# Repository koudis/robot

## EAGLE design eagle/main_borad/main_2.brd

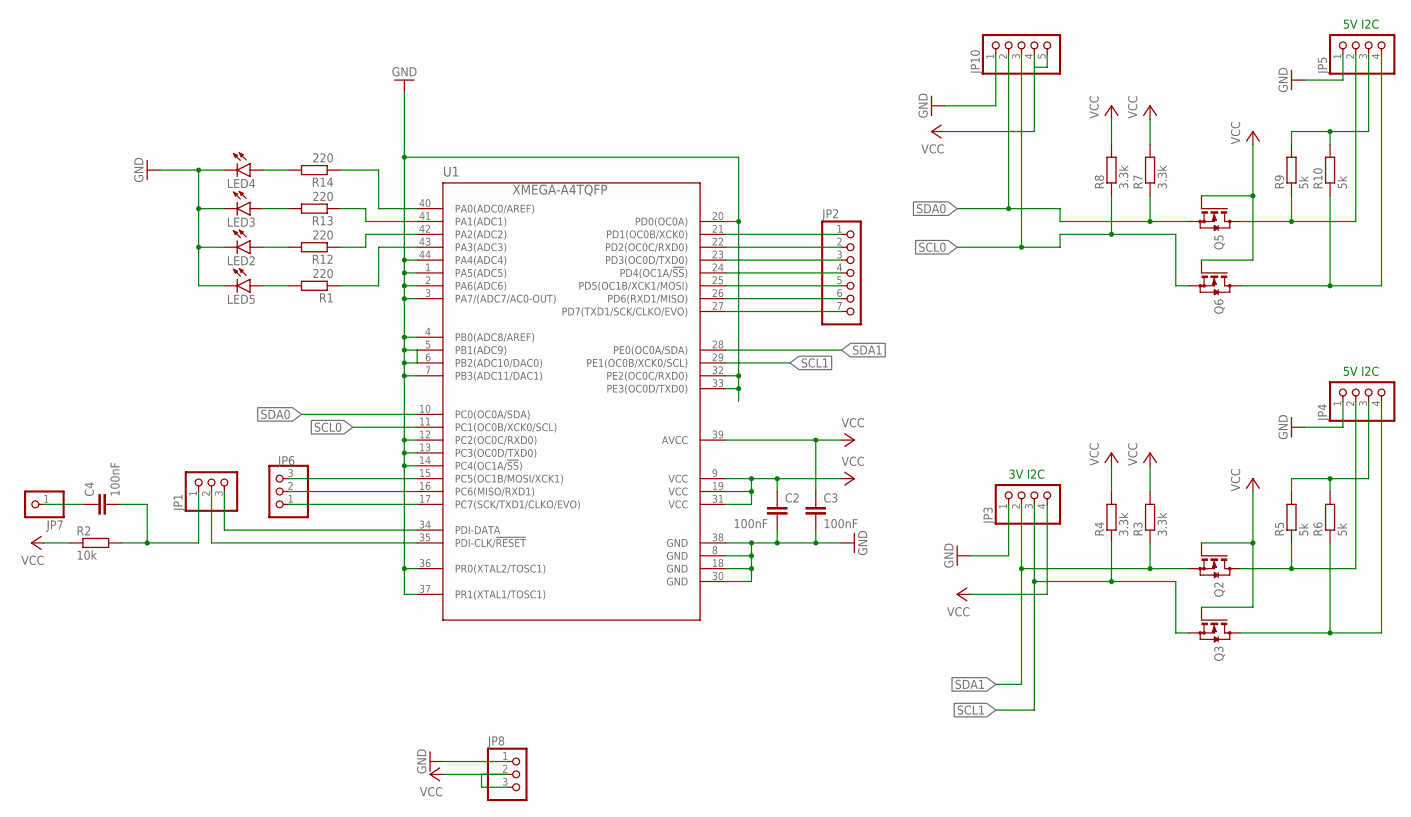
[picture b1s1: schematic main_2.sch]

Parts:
C2, C3, C4: 100nF; C0805
JP1, JP6, JP8: PINHD-1X3; 1X03
JP2: PINHD-1X7; 1X07
JP3, JP4, JP5: PINHD-1X4; 1X04
JP7: PINHD-1X1; 1X01
JP10: PINHD-1X5; 1X05
LED2, LED3, LED4, LED5: LED1206; LED-1206
Q2, Q3, Q5, Q6: BSS123; SOT23
R1, R12, R13, R14: 220; R0805
R2: 10k; R0805
R3, R4, R7, R8: 3.3k; R0805
R5, R6, R9, R10: 5k; R0805
U1: XMEGA-A4TQFP; TQFP44

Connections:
GND: C2.2, C3.2, JP3.1, JP4.1, JP5.1, JP8.1, JP10.1, LED2.C, LED3.C, LED4.C, LED5.C, U1.1 (PA5(ADC5)), U1.2 (PA6(ADC6)), U1.3 (PA7/(ADC7/AC0-OUT)), U1.4 (PB0(ADC8/AREF)), U1.5 (PB1(ADC9)), U1.6 (PB2(ADC10/DAC0)), U1.7 (PB3(ADC11/DAC1)), U1.8 (GND), U1.12 (PC2(OC0C/RXD0)), U1.13 (PC3(OC0D/TXD0)), U1.14 (PC4(OC1A/!SS!)), U1.18 (GND), U1.20 (PD0(OC0A)), U1.30 (GND), U1.32 (PE2(OC0C/RXD0)), U1.33 (PE3(OC0D/TXD0)), U1.36 (PR0(XTAL2/TOSC1)), U1.37 (PR1(XTAL1/TOSC1)), U1.38 (GND), U1.44 (PA4(ADC4))
unnamed: C4.2, JP1.1, R2.2
unnamed: JP1.2, U1.35 (PDI-CLK/!RESET)
unnamed: JP6.1, U1.17 (PC7(SCK/TXD1/CLKO/EVO))
unnamed: JP2.5, U1.25 (PD5(OC1B/XCK1/MOSI))
unnamed: JP2.6, U1.26 (PD6(RXD1/MISO))
unnamed: JP2.3, U1.23 (PD3(OC0D/TXD0))
unnamed: JP2.2, U1.22 (PD2(OC0C/RXD0))
unnamed: JP4.2, Q2.3 (D), R5.1
unnamed: JP4.4, Q3.3 (D), R6.1
unnamed: JP1.3, U1.34 (PDI-DATA)
unnamed: JP2.1, U1.21 (PD1(OC0B/XCK0))
unnamed: JP2.4, U1.24 (PD4(OC1A/!SS!))
unnamed: JP2.7, U1.27 (PD7(TXD1/SCK/CLKO/EVO))
unnamed: JP4.3, R5.2, R6.2
unnamed: JP6.2, U1.16 (PC6(MISO/RXD1))
unnamed: JP6.3, U1.15 (PC5(OC1B/MOSI/XCK1))
unnamed: JP5.2, Q5.3 (D), R9.1
unnamed: JP5.4, Q6.3 (D), R10.1
unnamed: JP5.3, R9.2, R10.2
unnamed: R1.1, U1.43 (PA3(ADC3))
unnamed: R12.1, U1.42 (PA2(ADC2))
unnamed: R13.1, U1.41 (PA1(ADC1))
unnamed: R14.1, U1.40 (PA0(ADC0/AREF))
unnamed: LED5.A, R1.2
unnamed: LED2.A, R12.2
unnamed: LED3.A, R13.2
unnamed: LED4.A, R14.2
RESET: C4.1, JP7.1
SCL0: JP10.3, Q6.2 (S), R8.1, U1.11 (PC1(OC0B/XCK0/SCL))
SCL1: JP3.3, Q3.2 (S), R4.1, U1.29 (PE1(OC0B/XCK0/SCL))
SDA0: JP10.2, Q5.2 (S), R7.1, U1.10 (PC0(OC0A/SDA))
SDA1: JP3.2, Q2.2 (S), R3.1, U1.28 (PE0(OC0A/SDA))
VCC: C2.1, C3.1, JP3.4, JP8.2, JP8.3, JP10.4, JP10.5, Q2.1 (G), Q3.1 (G), Q5.1 (G), Q6.1 (G), R2.1, R3.2, R4.2, R7.2, R8.2, U1.9 (VCC), U1.19 (VCC), U1.31 (VCC), U1.39 (AVCC)

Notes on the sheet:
5V I2C
3V I2C

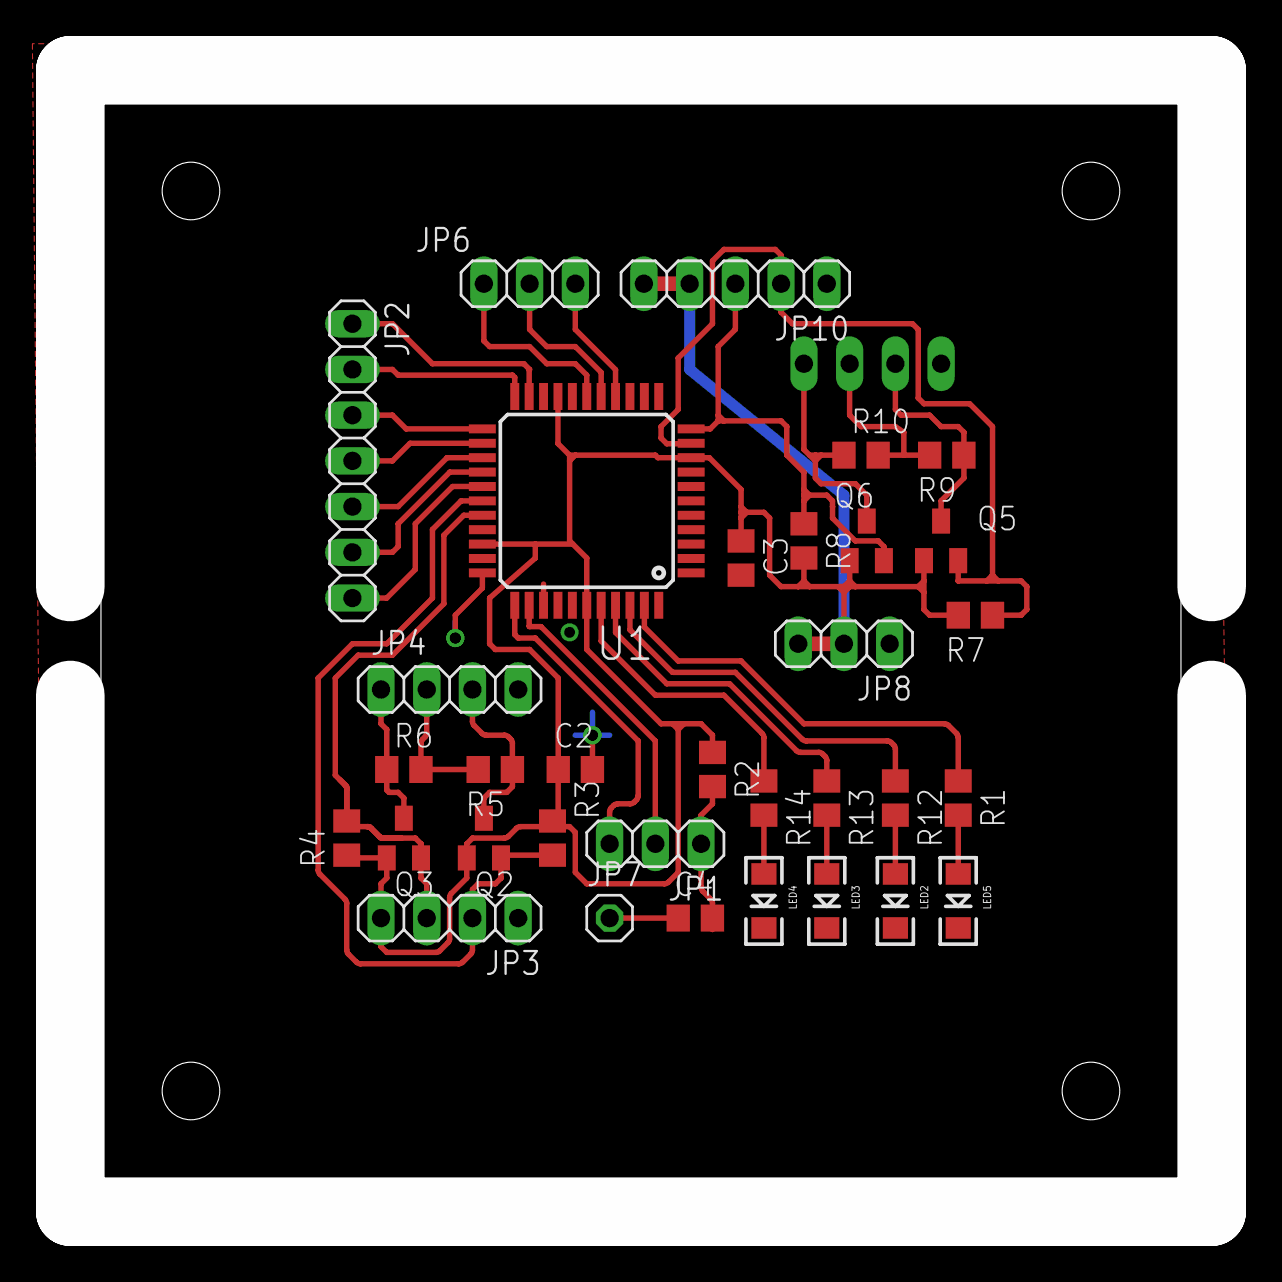
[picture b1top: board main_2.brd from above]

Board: 2 copper layers, 63.4 x 63.4 mm, 34 parts (1 on the bottom side), 34 nets.

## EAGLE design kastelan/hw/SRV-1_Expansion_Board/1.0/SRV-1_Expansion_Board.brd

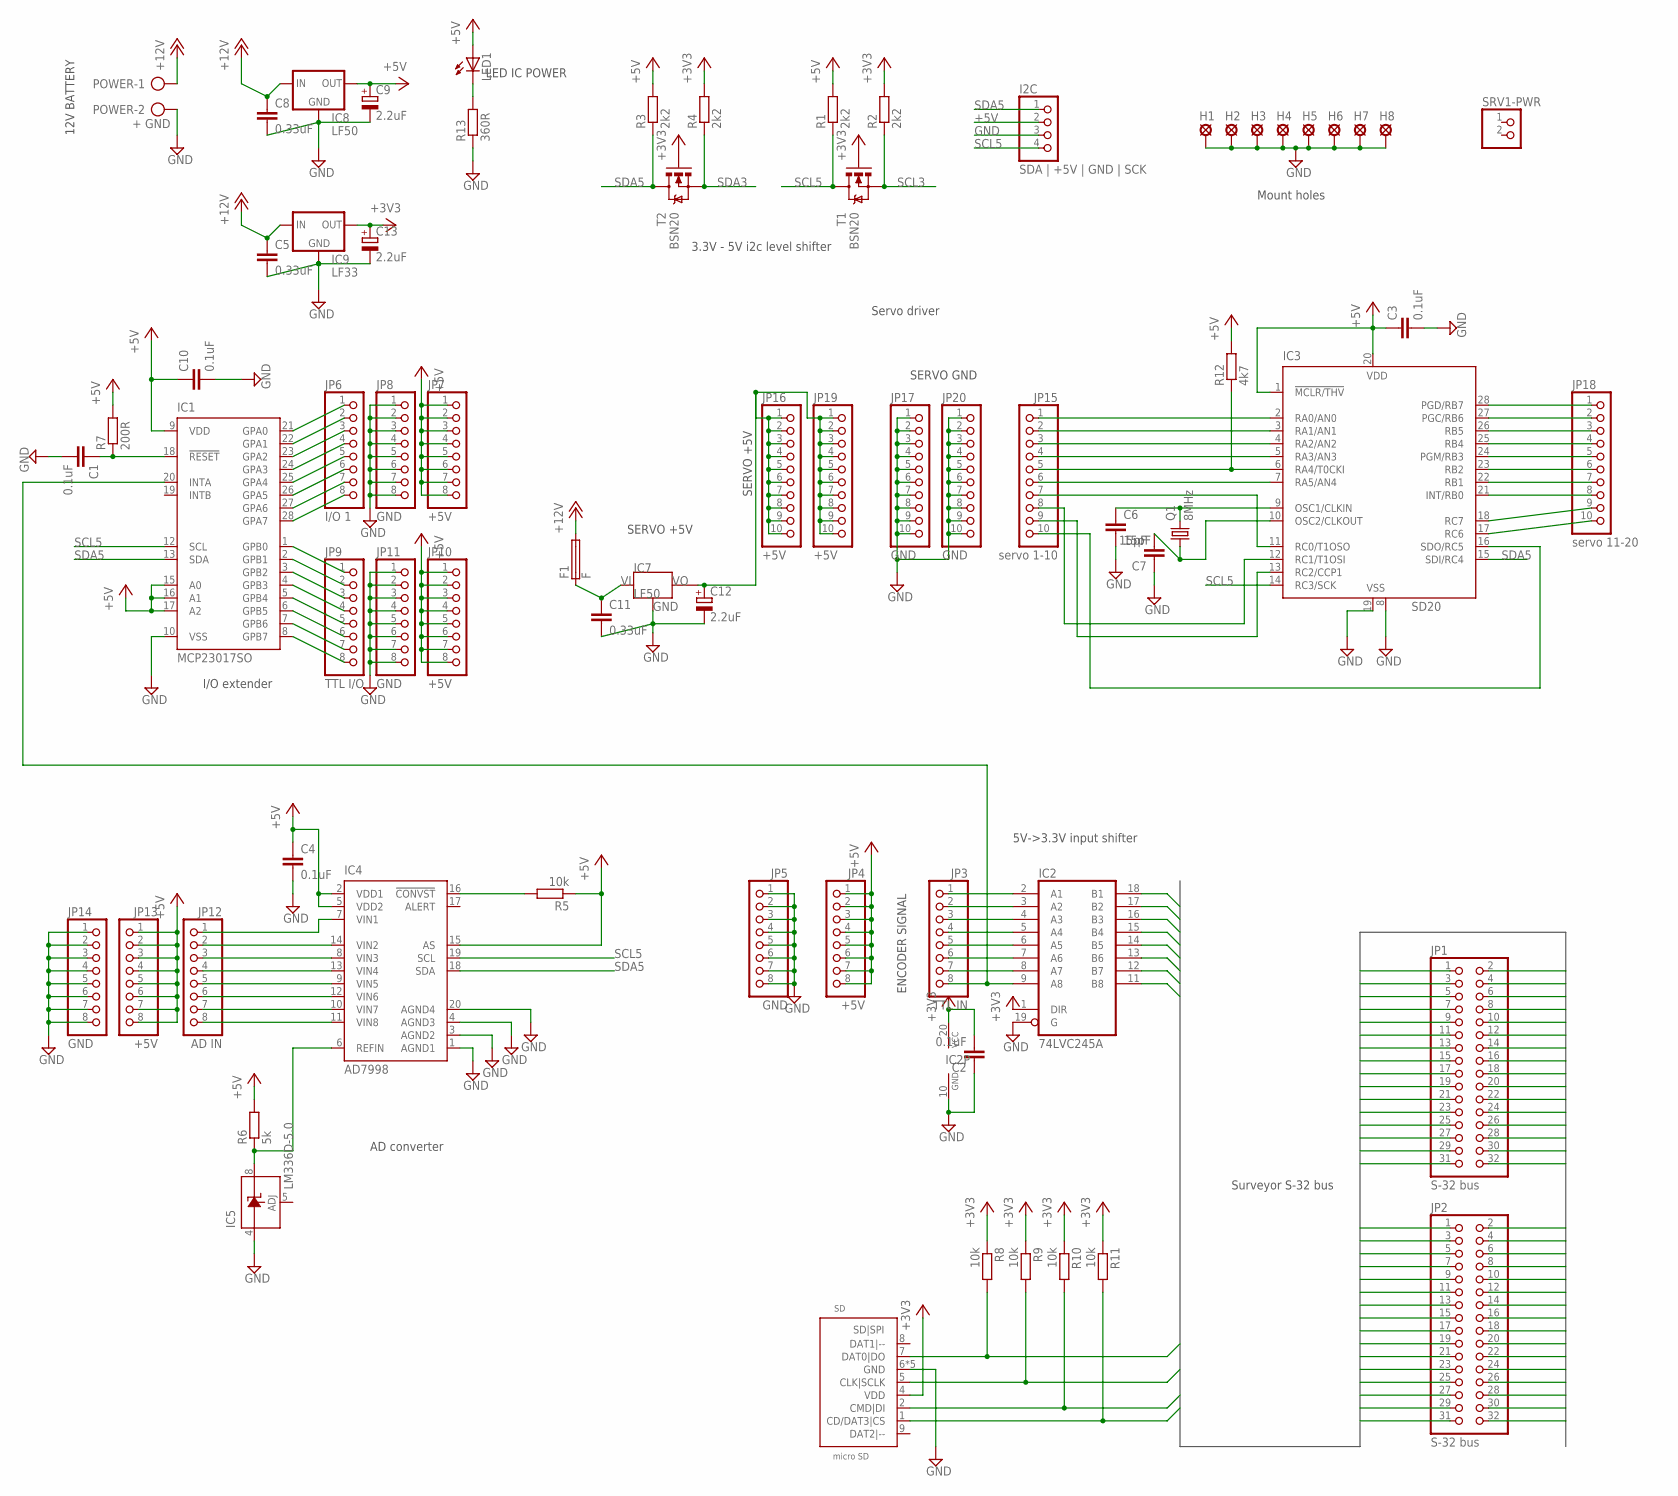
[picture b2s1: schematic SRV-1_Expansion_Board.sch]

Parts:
C1, C2, C3, C4, C10: 0.1uF; 1206
C5, C8, C11: 0.33uF; C025-024X044
C6, C7: 15pF; 1206
C9, C12, C13: 2.2uF; E1,8-4
F1: F; TE5
H1, H2, H3, H4: LSP35
H5, H6, H7, H8: LSP40
I2C: SDA | +5V | GND | SCK; 1X04
IC1: MCP23017SO; SO28W
IC2: 74LVC245A; SO20W
IC3: SD20; DIL28-3
IC4: AD7998; TSSOP20
IC5: LM336D-5.0; SO08
IC7: LF50; TO220V
IC8: LF50; DPAK
IC9: LF33; DPAK
JP1, JP2: S-32 bus; 2X16
JP3: TTL IN; 1X08
JP4, JP7, JP10, JP13: +5V; 1X08
JP5, JP8, JP11, JP14: GND; 1X08
JP6: I/O 1; 1X08
JP9: TTL I/O; 1X08
JP12: AD IN; 1X08
JP15: servo 1-10; 1X10
JP16, JP19: +5V; 1X10
JP17, JP20: GND; 1X10
JP18: servo 11-20; 1X10
LED1: LEDCHIPLED_1206; CHIPLED_1206
POWER: + GND; AK500/2
Q1: 8MHz; HC49U70
R1, R2, R3, R4: 2k2; R1206
R5, R8, R9, R10, R11: 10k; R1206
R6: 5k; R1206
R7: 200R; R1206
R12: 4k7; R1206
R13: 360R; R1206
SD: micro SD; SD-500901-0801
SRV1-PWR: PINHD-1X2; 1X02
T1, T2: BSN20; SOT23

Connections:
+3V3: C2.2, C13.+, IC2.1 (DIR), IC2.20 (VCC), IC9.3 (OUT), JP1.1, JP2.1, R2.2, R4.2, R8.1, R9.1, R10.1, R11.1, SD.4 (VDD), T1.1 (G), T2.1 (G)
+5V: C3.1, C4.1, C9.+, C10.1, I2C.2, IC1.9 (VDD), IC1.15 (A0), IC1.16 (A1), IC1.17 (A2), IC3.1 (!MCLR/THV), IC3.20 (VDD), IC4.2 (VDD1), IC4.5 (VDD2), IC4.15 (AS), IC8.3 (OUT), JP4.1, JP4.2, JP4.3, JP4.4, JP4.5, JP4.6, JP4.7, JP4.8, JP7.1, JP7.2, JP7.3, JP7.4, JP7.5, JP7.6, JP7.7, JP7.8, JP10.1, JP10.2, JP10.3, JP10.4, JP10.5, JP10.6, JP10.7, JP10.8, JP13.1, JP13.2, JP13.3, JP13.4, JP13.5, JP13.6, JP13.7, JP13.8, LED1.A, R1.2, R3.2, R5.1, R6.2, R7.2, R12.2
+12V: C5.1, C8.1, F1.2, IC8.1 (IN), IC9.1 (IN), POWER.1
GND: C1.2, C2.1, C3.2, C4.2, C5.2, C6.2, C7.1, C8.2, C9.-, C10.2, C11.2, C12.-, C13.-, H1.MP, H2.MP, H3.MP, H4.MP, H5.MP, H6.MP, H7.MP, H8.MP, I2C.3, IC1.10 (VSS), IC2.10 (GND), IC2.19 (G), IC3.8 (VSS), IC3.19 (VSS), IC4.1 (AGND1), IC4.3 (AGND2), IC4.4 (AGND3), IC4.20 (AGND4), IC5.4 (A), IC7.3 (GND), IC8.2 (GND), IC9.2 (GND), JP1.2, JP1.16, JP2.2, JP2.16, JP5.1, JP5.2, JP5.3, JP5.4, JP5.5, JP5.6, JP5.7, JP5.8, JP8.1, JP8.2, JP8.3, JP8.4, JP8.5, JP8.6, JP8.7, JP8.8, JP11.1, JP11.2, JP11.3, JP11.4, JP11.5, JP11.6, JP11.7, JP11.8, JP14.1, JP14.2, JP14.3, JP14.4, JP14.5, JP14.6, JP14.7, JP14.8, JP17.1, JP17.2, JP17.3, JP17.4, JP17.5, JP17.6, JP17.7, JP17.8, JP17.9, JP17.10, JP20.1, JP20.2, JP20.3, JP20.4, JP20.5, JP20.6, JP20.7, JP20.8, JP20.9, JP20.10, POWER.2, R13.1, SD.6 (GND), SD.GND1 (GND), SD.GND2 (GND), SD.GND3 (GND), SD.GND4 (GND)
unnamed: IC4.16 (!CONVST), R5.2
unnamed: C11.1, F1.1, IC7.1 (IN)
unnamed: IC1.21 (GPA0), JP6.1
unnamed: C6.1, IC3.9 (OSC1/CLKIN), Q1.2
unnamed: C7.2, IC3.10 (OSC2/CLKOUT), Q1.1
unnamed: IC1.20 (INTA), IC2.9 (A8), JP3.8
unnamed: IC1.22 (GPA1), JP6.2
unnamed: IC4.6 (REFIN), IC5.8 (C), R6.1
unnamed: IC3.2 (RA0/AN0), JP15.1
unnamed: IC1.23 (GPA2), JP6.3
unnamed: IC1.24 (GPA3), JP6.4
unnamed: IC1.25 (GPA4), JP6.5
unnamed: C1.1, IC1.18 (!RESET), R7.1
unnamed: IC1.26 (GPA5), JP6.6
unnamed: IC1.27 (GPA6), JP6.7
unnamed: IC1.28 (GPA7), JP6.8
unnamed: IC1.1 (GPB0), JP9.1
unnamed: IC1.2 (GPB1), JP9.2
unnamed: IC1.3 (GPB2), JP9.3
unnamed: IC1.4 (GPB3), JP9.4
unnamed: IC1.5 (GPB4), JP9.5
unnamed: IC1.6 (GPB5), JP9.6
unnamed: IC1.7 (GPB6), JP9.7
unnamed: IC1.8 (GPB7), JP9.8
unnamed: IC3.16 (SDO/RC5), JP15.10
unnamed: IC2.2 (A1), JP3.1
unnamed: IC2.3 (A2), JP3.2
unnamed: IC2.4 (A3), JP3.3
unnamed: IC2.5 (A4), JP3.4
unnamed: IC2.6 (A5), JP3.5
unnamed: IC2.7 (A6), JP3.6
unnamed: IC2.8 (A7), JP3.7
unnamed: IC4.11 (VIN8), JP12.8
unnamed: IC3.3 (RA1/AN1), JP15.2
unnamed: IC3.4 (RA2/AN2), JP15.3
unnamed: IC3.5 (RA3/AN3), JP15.4
unnamed: IC3.6 (RA4/T0CKI), JP15.5, R12.1
unnamed: IC3.7 (RA5/AN4), JP15.6
unnamed: IC3.11 (RC0/T1OSO), JP15.7
unnamed: IC3.12 (RC1/T1OSI), JP15.8
unnamed: IC3.13 (RC2/CCP1), JP15.9
unnamed: IC3.28 (PGD/RB7), JP18.1
unnamed: IC3.27 (PGC/RB6), JP18.2
unnamed: IC3.26 (RB5), JP18.3
unnamed: IC3.25 (RB4), JP18.4
unnamed: IC3.24 (PGM/RB3), JP18.5
unnamed: IC3.23 (RB2), JP18.6
unnamed: IC3.22 (RB1), JP18.7
unnamed: IC3.21 (INT/RB0), JP18.8
unnamed: IC3.18 (RC7), JP18.9
unnamed: IC3.17 (RC6), JP18.10
unnamed: IC4.7 (VIN1), JP12.1
unnamed: IC4.14 (VIN2), JP12.2
unnamed: IC4.8 (VIN3), JP12.3
unnamed: IC4.13 (VIN4), JP12.4
unnamed: IC4.9 (VIN5), JP12.5
unnamed: IC4.12 (VIN6), JP12.6
unnamed: IC4.10 (VIN7), JP12.7
unnamed: LED1.C, R13.2
S-32-BUS3: JP1.3, JP2.3
S-32-BUS4: JP1.4, JP2.4
S-32-BUS5: JP1.5, JP2.5
S-32-BUS6: JP1.6, JP2.6
S-32-BUS7: JP1.7, JP2.7
S-32-BUS8: JP1.8, JP2.8
S-32-BUS9: JP1.9, JP2.9, R10.2, SD.2 (CMD|DI)
S-32-BUS10: JP1.10, JP2.10, R8.2, SD.7 (DAT0|DO)
S-32-BUS11: JP1.11, JP2.11, R9.2, SD.5 (CLK|SCLK)
S-32-BUS12: JP1.12, JP2.12, R11.2, SD.1 (CD/DAT3|CS)
S-32-BUS13: JP1.13, JP2.13
S-32-BUS17: JP1.17, JP2.17
S-32-BUS18: JP1.18, JP2.18
S-32-BUS19: JP1.19, JP2.19
S-32-BUS20: JP1.20, JP2.20
S-32-BUS21: JP1.21, JP2.21
S-32-BUS22: JP1.22, JP2.22
S-32-BUS23: JP1.23, JP2.23
S-32-BUS24: JP1.24, JP2.24
S-32-BUS25: IC2.18 (B1), JP1.25, JP2.25
S-32-BUS26: IC2.17 (B2), JP1.26, JP2.26
S-32-BUS27: IC2.16 (B3), JP1.27, JP2.27
S-32-BUS28: IC2.15 (B4), JP1.28, JP2.28
S-32-BUS29: IC2.14 (B5), JP1.29, JP2.29
S-32-BUS30: IC2.13 (B6), JP1.30, JP2.30
S-32-BUS31: IC2.12 (B7), JP1.31, JP2.31
S-32-BUS32: IC2.11 (B8), JP1.32, JP2.32
SCL3: JP1.14, JP2.14, R2.1, T1.2 (S)
SCL5: I2C.4, IC1.12 (SCL), IC3.14 (RC3/SCK), IC4.19 (SCL), R1.1, T1.3 (D)
SDA3: JP1.15, JP2.15, R4.1, T2.2 (S)
SDA5: I2C.1, IC1.13 (SDA), IC3.15 (SDI/RC4), IC4.18 (SDA), R3.1, T2.3 (D)
SERVO2+5V: C12.+, IC7.2 (OUT), JP16.1, JP16.2, JP16.3, JP16.4, JP16.5, JP16.6, JP16.7, JP16.8, JP16.9, JP16.10, JP19.1, JP19.2, JP19.3, JP19.4, JP19.5, JP19.6, JP19.7, JP19.8, JP19.9, JP19.10

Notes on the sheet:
SERVO GND
12V BATTERY
SERVO +5V
LED IC POWER
ENCODER SIGNAL
3.3V - 5V i2c level shifter
Servo driver
AD converter
I/O extender
5V->3.3V input shifter
Surveyor S-32 bus
SERVO +5V
Mount holes

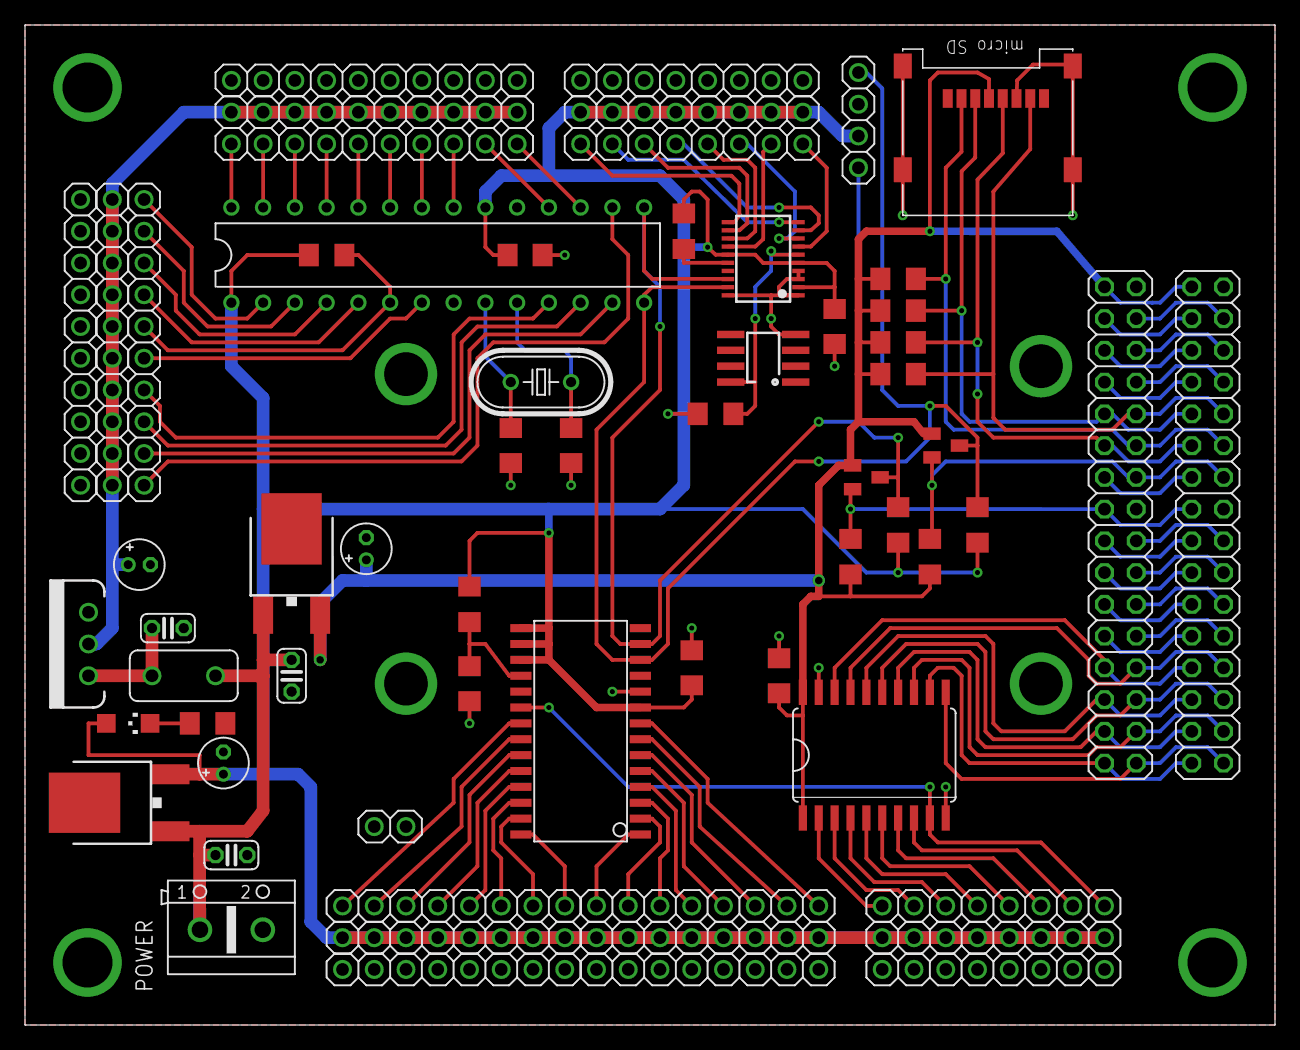
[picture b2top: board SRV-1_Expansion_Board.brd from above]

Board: 2 copper layers, 100.0 x 80.0 mm, 71 parts (0 on the bottom side), 95 nets.

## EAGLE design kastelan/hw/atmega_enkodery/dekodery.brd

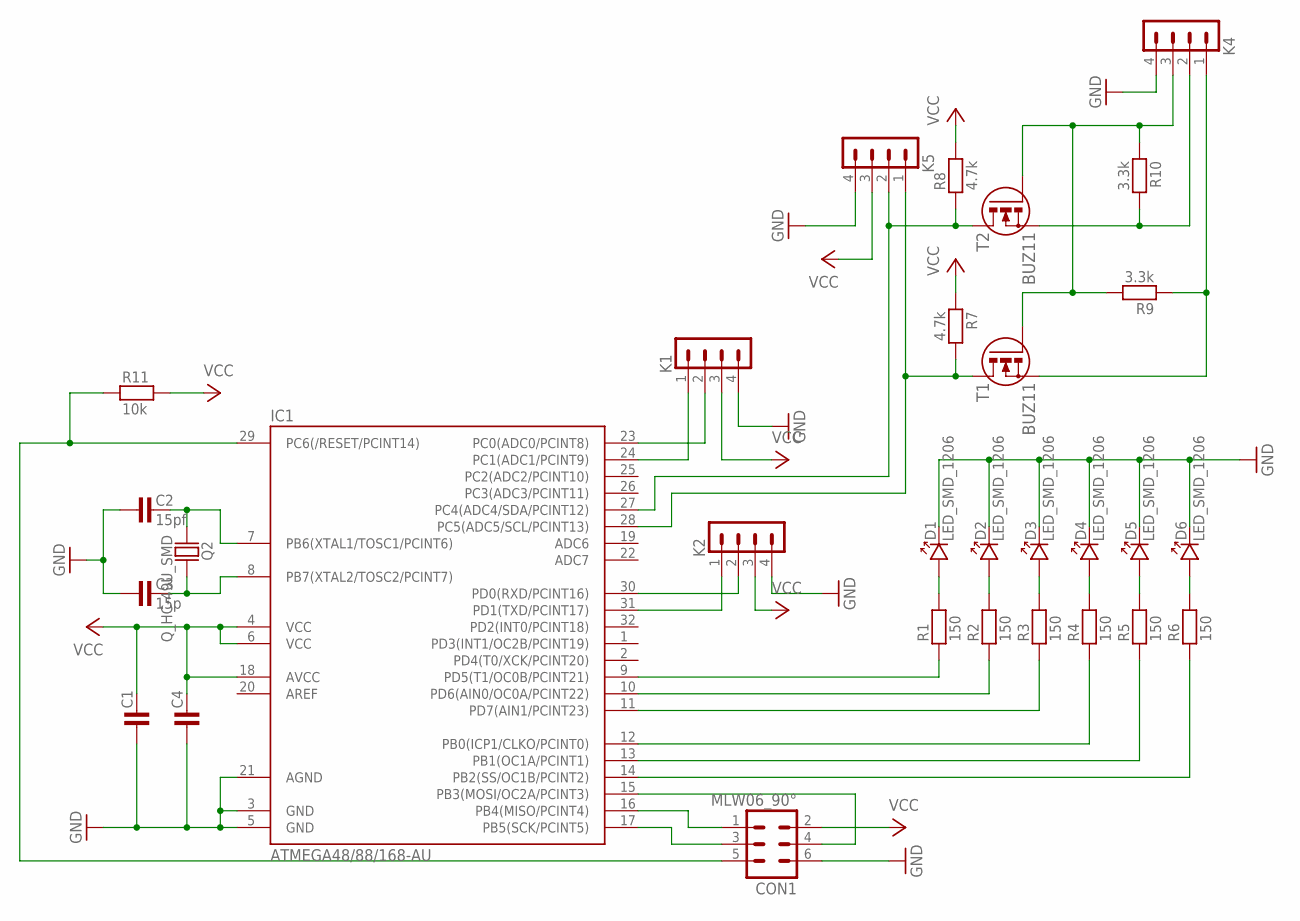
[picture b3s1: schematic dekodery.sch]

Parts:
C1, C4: C-KERAMIK_SMD_1206; 1206
C2: 15pf; 1206
C3: 15p; 1206
CON1: MLW06_90°; MLW06A
D1, D2, D3, D4, D5, D6: LED_SMD_1206; P1206
IC1: ATMEGA48/88/168-AU; TQFP32-08
K1, K2, K4, K5: PSH02-04W
Q2: Q_HC-49U_SMD; HC-49US
R1, R2, R3, R4, R5, R6: 150; 1206
R7, R8: 4.7k; 1206
R9, R10: 3.3k; 1206
R11: 10k; 1206
T1, T2: BUZ11; SOT23

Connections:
GND: C1.1, C2.1, C3.1, C4.1, CON1.6, D1.K, D2.K, D3.K, D4.K, D5.K, D6.K, IC1.3 (GND), IC1.5 (GND), IC1.21 (AGND), K1.4, K2.4, K4.4, K5.4
unnamed: IC1.30 (PD0(RXD/PCINT16)), K2.2
unnamed: IC1.31 (PD1(TXD/PCINT17)), K2.1
unnamed: IC1.23 (PC0(ADC0/PCINT8)), K1.2
unnamed: IC1.24 (PC1(ADC1/PCINT9)), K1.1
unnamed: IC1.28 (PC5(ADC5/SCL/PCINT13)), K5.1, R7.2, T1.3 (D)
unnamed: C3.2, IC1.8 (PB7(XTAL2/TOSC2/PCINT7)), Q2.2
unnamed: CON1.1, IC1.16 (PB4(MISO/PCINT4))
unnamed: CON1.3, IC1.17 (PB5(SCK/PCINT5))
unnamed: CON1.4, IC1.15 (PB3(MOSI/OC2A/PCINT3))
unnamed: IC1.9 (PD5(T1/OC0B/PCINT21)), R1.1
unnamed: IC1.10 (PD6(AIN0/OC0A/PCINT22)), R2.1
unnamed: IC1.11 (PD7(AIN1/PCINT23)), R3.1
unnamed: IC1.12 (PB0(ICP1/CLKO/PCINT0)), R4.1
unnamed: IC1.13 (PB1(OC1A/PCINT1)), R5.1
unnamed: IC1.14 (PB2(SS/OC1B/PCINT2)), R6.1
unnamed: D1.A, R1.2
unnamed: D6.A, R6.2
unnamed: D5.A, R5.2
unnamed: D4.A, R4.2
unnamed: D3.A, R3.2
unnamed: D2.A, R2.2
unnamed: C2.2, IC1.7 (PB6(XTAL1/TOSC1/PCINT6)), Q2.1
unnamed: IC1.27 (PC4(ADC4/SDA/PCINT12)), K5.2, R8.1, T2.3 (D)
unnamed: K4.3, R9.2, R10.1, T1.1 (G), T2.1 (G)
unnamed: K4.2, R10.2, T2.2 (S)
unnamed: K4.1, R9.1, T1.2 (S)
RST: CON1.5, IC1.29 (PC6(/RESET/PCINT14)), R11.1
VCC: C1.2, C4.2, CON1.2, IC1.4 (VCC), IC1.6 (VCC), IC1.18 (AVCC), K1.3, K2.3, K5.3, R7.1, R8.2, R11.2

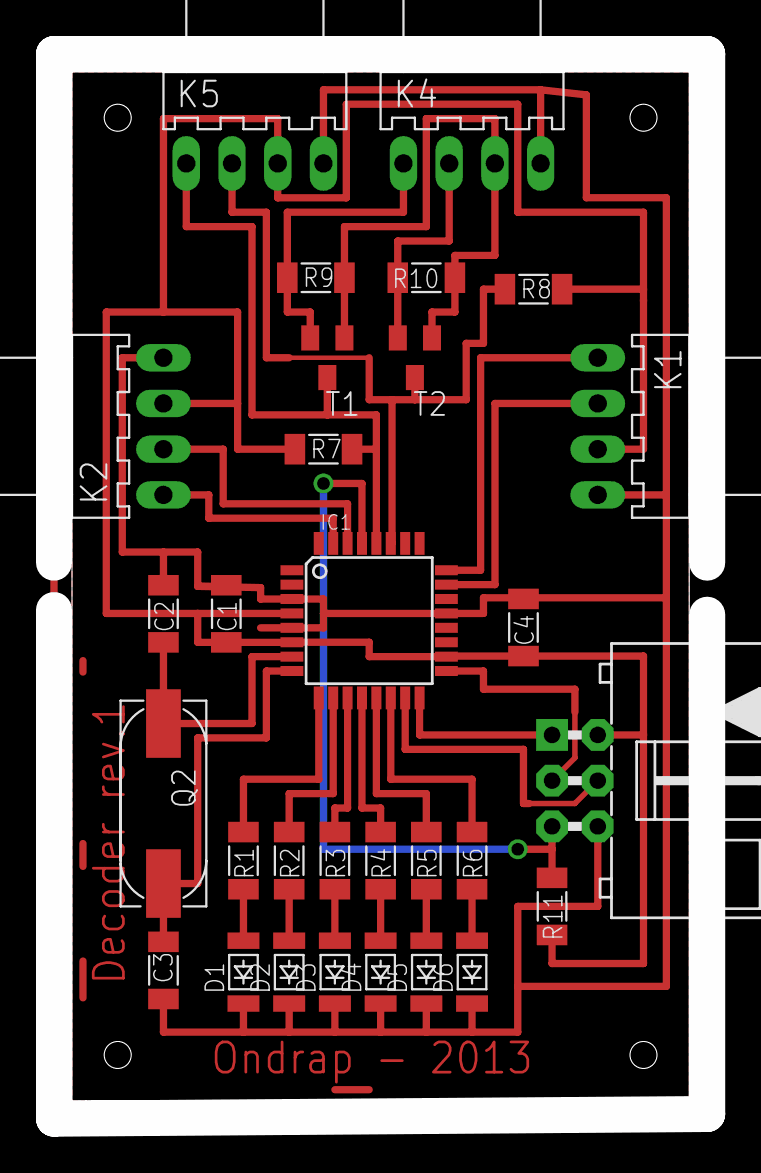
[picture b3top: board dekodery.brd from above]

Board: 2 copper layers, 36.3 x 59.1 mm, 30 parts (0 on the bottom side), 29 nets.

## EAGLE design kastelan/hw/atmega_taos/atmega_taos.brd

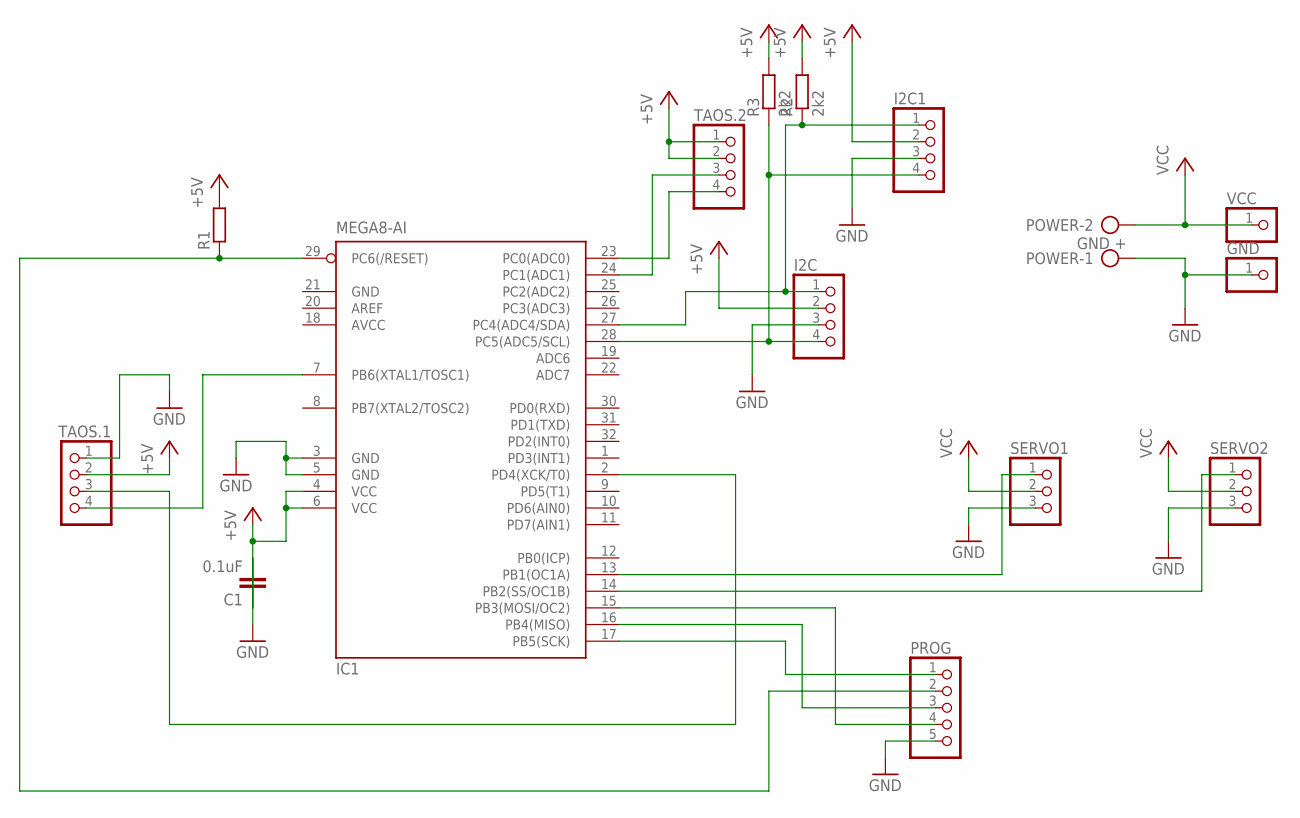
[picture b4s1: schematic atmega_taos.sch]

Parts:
C1: 0.1uF; 0805BIG
GND: PINHD-1X1; 1X01
I2C, I2C1: PINHD-1X4; 1X04
IC1: MEGA8-AI; TQFP32-08
POWER: GND +; AK500/2
PROG: PINHD-1X5; 1X05
R1: RESISTORR-0805BIG; 0805BIG
R2, R3: 2k2; 0805BIG
SERVO1, SERVO2: PINHD-1X3; 1X03
TAOS.1, TAOS.2: PINHD-1X4; 1X04
VCC: PINHD-1X1; 1X01

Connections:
+5V: C1.1, I2C.2, I2C1.2, IC1.4 (VCC), IC1.6 (VCC), R1.2, R2.2, R3.2, TAOS.1.2, TAOS.2.1, TAOS.2.2
AVCC: IC1.18 (AVCC)
GND: C1.2, GND.1, I2C.3, I2C1.3, IC1.3 (GND), IC1.5 (GND), IC1.21 (GND), POWER.1, PROG.5, SERVO1.3, SERVO2.3, TAOS.1.1
unnamed: IC1.13 (PB1(OC1A)), SERVO1.1
unnamed: I2C.1, I2C1.1, IC1.27 (PC4(ADC4/SDA)), R2.1
unnamed: IC1.2 (PD4(XCK/T0)), TAOS.1.3
unnamed: IC1.24 (PC1(ADC1)), TAOS.2.3
unnamed: IC1.23 (PC0(ADC0)), TAOS.2.4
unnamed: I2C.4, I2C1.4, IC1.28 (PC5(ADC5/SCL)), R3.1
unnamed: IC1.14 (PB2(SS/OC1B)), SERVO2.1
unnamed: IC1.7 (PB6(XTAL1/TOSC1)), TAOS.1.4
unnamed: IC1.15 (PB3(MOSI/OC2)), PROG.4
unnamed: IC1.29 (PC6(/RESET)), PROG.2, R1.1
unnamed: IC1.17 (PB5(SCK)), PROG.1
unnamed: IC1.16 (PB4(MISO)), PROG.3
VCC: POWER.2, SERVO1.2, SERVO2.2, VCC.1

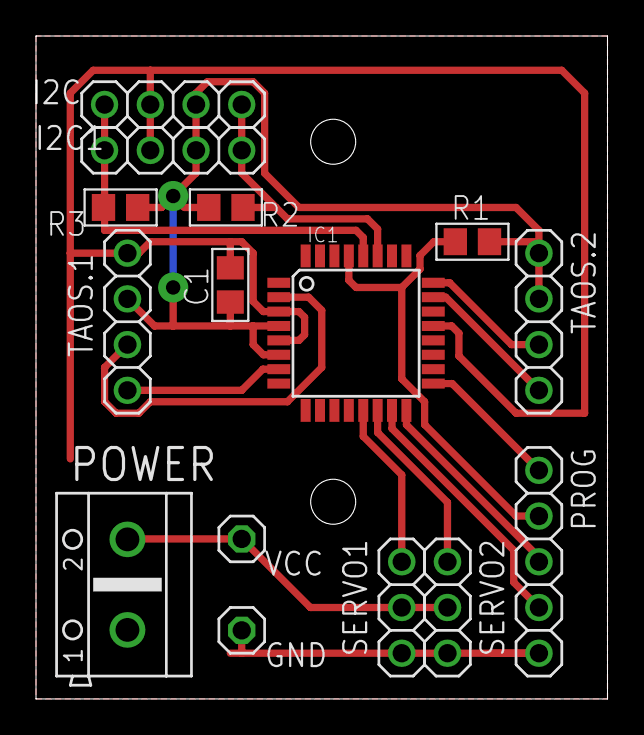
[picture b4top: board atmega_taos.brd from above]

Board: 2 copper layers, 31.8 x 36.8 mm, 15 parts (0 on the bottom side), 15 nets.

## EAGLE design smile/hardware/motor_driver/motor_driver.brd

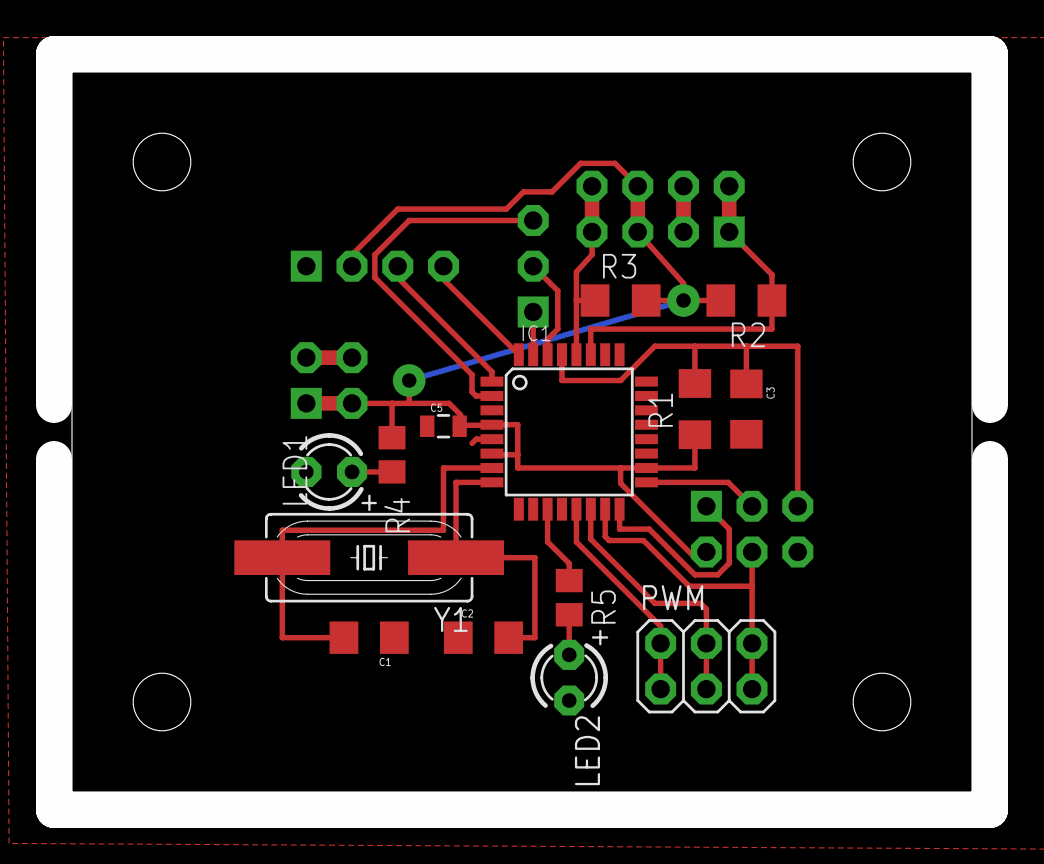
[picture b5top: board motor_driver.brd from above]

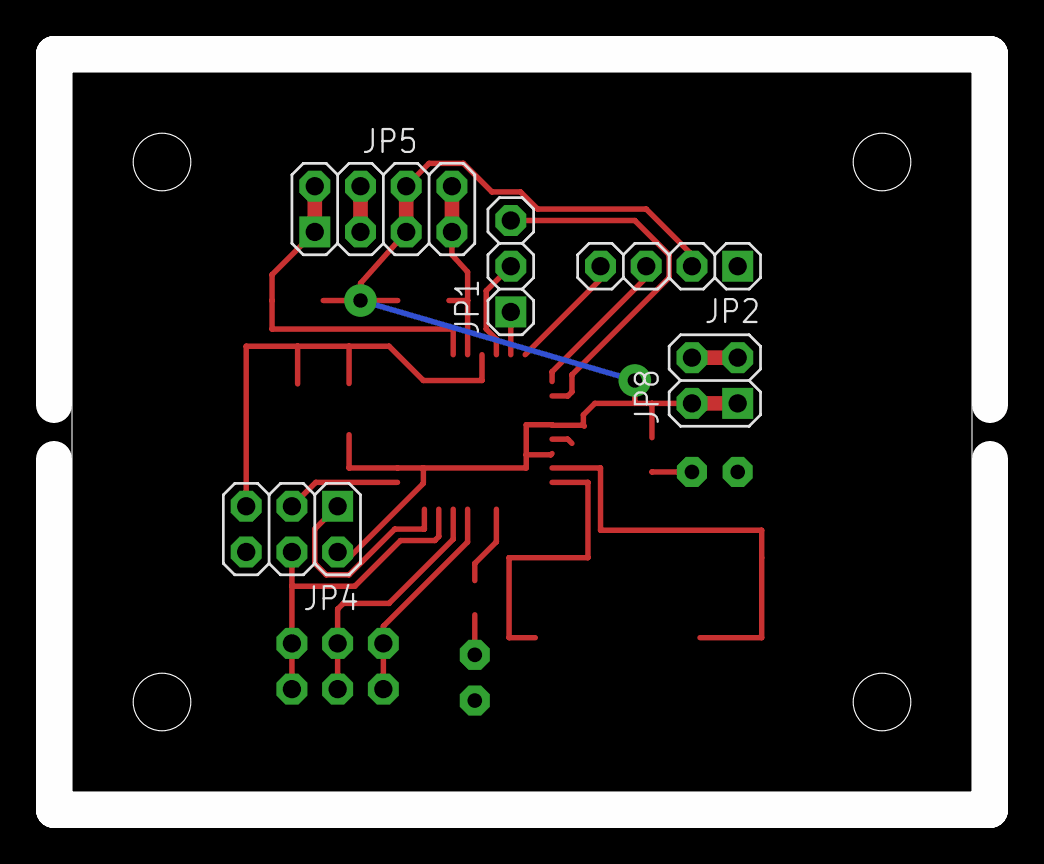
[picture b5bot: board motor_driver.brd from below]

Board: 2 copper layers, 52.0 x 42.0 mm, 19 parts (5 on the bottom side), 20 nets.

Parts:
C1, C2: 22pF; 1206
C3: 4n7; 1206
C5: 220nF; 0805
IC1: MEGA8-AI; TQFP32-08
JP1: serial; 1X03-S
JP2: encoder; 1X04-S
JP4: ICSP; 2X03
JP5: i2c; 2X04
JP8: power; 2X02
LED1: OF-SMD-2012G-1; LED3MM
LED2: OF-SMD2012R; LED3MM
PWM: 2X03
R1: 10k; R1206
R2, R3: 4k7; R1206
R4: 150k; R0805
R5: 22k; R0805
Y1: 16MHz; HC49UP

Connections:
GND: C1.1, C2.1, C3.2, C5.1, IC1.3, IC1.5, IC1.21, JP2.1, JP4.6, JP5.3, JP5.4, JP8.3, JP8.4, LED1.K, LED2.K
INT0: IC1.32, JP2.4
INT1: IC1.1, JP2.3
MOSI/PWM2: IC1.15, JP4.4, PWM.5, PWM.6
unnamed: IC1.31, JP1.1
unnamed: C2.2, IC1.8, Y1.1
unnamed: C1.2, IC1.7, Y1.2
unnamed: IC1.11, R5.1
unnamed: IC1.30, JP1.2
unnamed: IC1.2, JP1.3
unnamed: IC1.28, JP5.7, JP5.8, R3.1
unnamed: IC1.27, JP5.1, JP5.2, R2.1
unnamed: LED1.A, R4.2
unnamed: IC1.17, JP4.3
unnamed: IC1.16, JP4.1
unnamed: LED2.A, R5.2
PWM1A: IC1.13, PWM.1, PWM.2
PWM1B: IC1.14, PWM.3, PWM.4
RESET: C3.1, IC1.29, JP4.5, R1.2
VCC: C5.2, IC1.4, IC1.6, IC1.18, JP2.2, JP4.2, JP5.5, JP5.6, JP8.1, JP8.2, R1.1, R2.2, R3.2, R4.1

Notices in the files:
parts and their libraries:
SparkFun-LED: Licensing: Creative Commons ShareAlike 4.0 International - https://creativecommons.org/licenses/by-sa/4.0
SparkFun: Licensing: CC v3.0 Share-Alike You are welcome to use this library for commercial purposes.
Copyright (C) PaJa 2011
Copyright (C) PaJa 2001-2011
